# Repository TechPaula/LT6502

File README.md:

# GITHUB PROJECT NOW DEAD
I've now moved away from Micros**t and it's AI slop.

Find this project here - (https://codeberg.org/TechPaula/)

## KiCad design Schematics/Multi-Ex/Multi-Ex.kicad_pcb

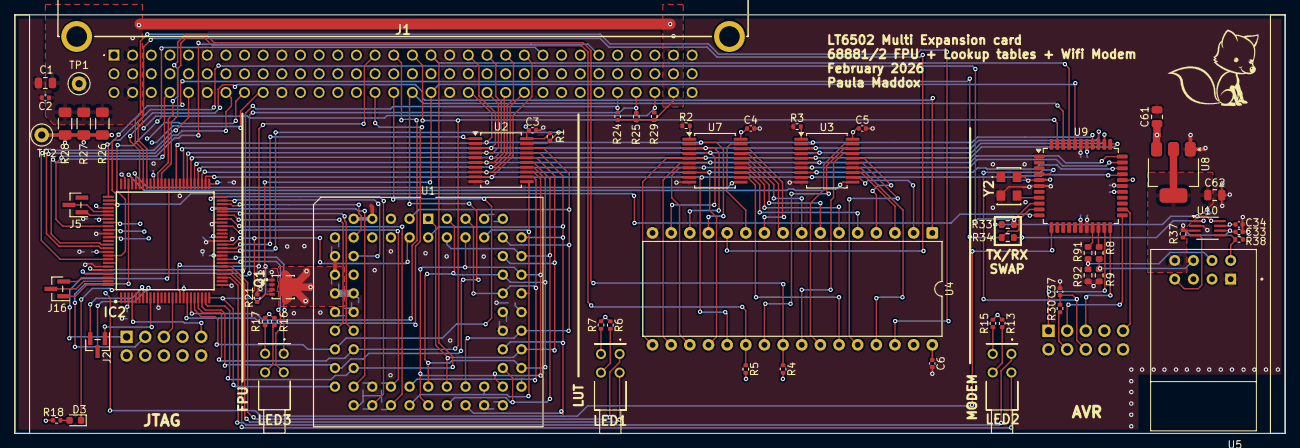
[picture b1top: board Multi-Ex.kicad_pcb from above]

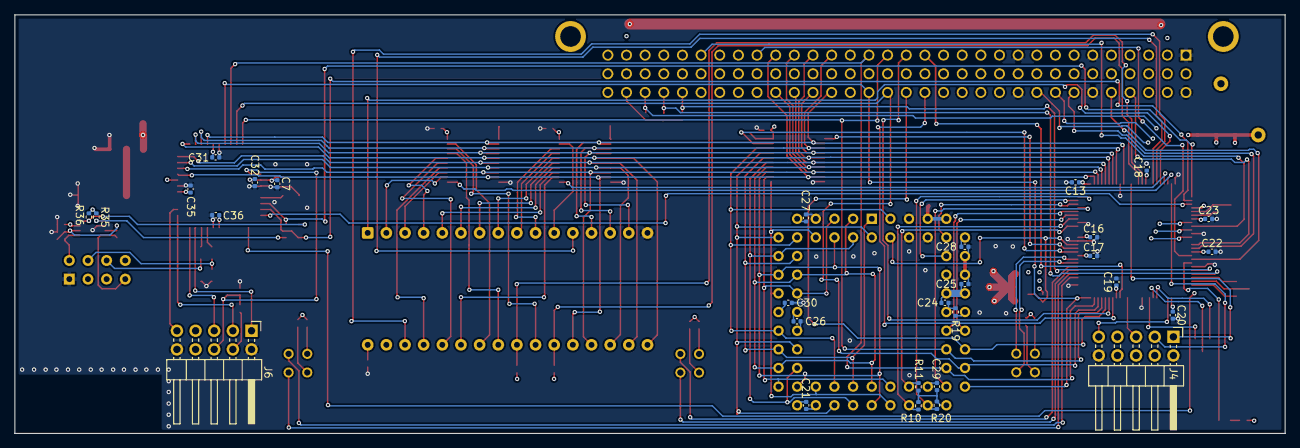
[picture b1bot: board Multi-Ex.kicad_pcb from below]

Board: 4 copper layers, 173.0 x 57.0 mm, 91 parts (29 on the bottom side), 120 nets.

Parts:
C1: 22uF 25V; C_0805_2012Metric
C2, C3, C4, C5, C6, C7, C13, C16, C17, C18, C19, C20, C21, C22, C23, C24, C25, C26, C27, C28, C29, C30, C31, C32, C33, C34, C35, C36, C37: 100nF; C_0402_1005Metric
C61, C62: 10uF NP; C_0805_2012Metric
D3: LED; LED_0603_1608Metric
FOX1: SYM_Flash_Large; Fox_avatar_18mm
IC2: ATF1508AS-7AX100; QFP50P1600X1600X120-100N
J1: DIN41612_02x32_AC(CAPS); 86093967113745ELF
J2, J5, J16: Conn_01x03; PinHeader_1x03_P1.00mm_Vertical_SMD_Pin1Left
J4, J6: Conn_02x05_Odd_Even; PinHeader_2x05_P2.54mm_Horizontal
LED1, LED2, LED3: LTL-42D1NMHDP1; LTL42D1NMHDP1
Q1: STL9P3LLH6; STL20N6F7
R1, R4, R5, R10, R11, R20, R24, R25, R29, R30, R35, R36, R37, R38: 10K; R_0402_1005Metric
R2, R3, R19: 0R; R_0402_1005Metric
R6, R7, R13, R15, R16, R17, R18: 470R; R_0402_1005Metric
R8, R91: 1K8; R_0603_1608Metric
R9, R92: 3K3; R_0603_1608Metric
R21: 100K; R_0402_1005Metric
R26, R27, R28: 0R; R_1206_3216Metric_Pad1.30x1.75mm_HandSolder
R33, R34: 0R; R_0603_1608Metric
TP1, TP2: TestPoint; TestPoint_Loop_D1.80mm_Drill1.0mm_Beaded
U1: MC68882_PLCC_68; PLCC-68_THT-Socket
U2: 74HC245; SSOP-20_5.3x7.2mm_P0.65mm
U3, U7: 74LS573; SSOP-20_5.3x7.2mm_P0.65mm
U4: SST39SF040; DIP-32_W15.24mm
U5: ESP8266-01_ESP-01; XCVR_ESP8266-01_ESP-01
U8: AMS1117-3.3; SOT-223-3_TabPin2
U9: ATmega644P-20A; TQFP-44_10x10mm_P0.8mm
U10: TXS0102DCT; SSOP-8_2.95x2.8mm_P0.65mm
Y2: ECS-3961-200-AU-TR; ECS3961200AUTR

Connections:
+3.3V: C33.1, C62.1, R37.1, R38.1, U5.8 (VCC), U8.2 (VO), U10.3 (VCCA), U10.6 (OE)
+5V: C3.1, C4.1, C5.1, C6.1, C7.1, C13.1, C16.1, C17.1, C18.1, C19.1, C20.1, C22.1, C23.1, C31.1, C32.1, C34.1, C35.1, C36.1, C61.1, IC2.3 (VCCIO_1), IC2.18 (VCCIO_2), IC2.34 (VCCIO_3), IC2.39 (VCCINT_1), IC2.51 (VCCIO_4), IC2.66 (VCCIO_5), IC2.82 (VCCIO_6), IC2.91 (VCCINT_2), J4.4, J6.4, Q1.1 (S_1), Q1.2 (S_2), Q1.3 (S_3), R1.2, R4.2, R5.2, R6.1, R7.2, R13.1, R15.2, R16.1, R17.2, R18.2, R21.1, R26.2, R27.2, R28.2, R30.1, R35.1, R36.1, TP2.1, U2.20 (VCC), U3.20 (VCC), U4.32 (VCC), U7.20 (VCC), U8.3 (VI), U9.5 (VCC), U9.17 (VCC), U9.27 (AVCC), U9.29 (AREF), U9.38 (VCC), U10.7 (VCCB), Y2.4 (VDD)
/Connector/A0: IC2.25 (I/O_19), J1.C18, U1.26 (A0), U9.40 (PB0)
/Connector/A1: IC2.24 (I/O_18), J1.A18, U1.25 (A1), U9.41 (PB1)
/Connector/A2: IC2.23 (I/O_17), J1.C17, U1.24 (A2), U9.42 (PB2)
/Connector/A3: IC2.22 (I/O_16), J1.A17, U1.23 (A3), U9.43 (PB3)
/Connector/A4: IC2.21 (I/O_15), J1.C16, U1.22 (A4)
/Connector/A5: IC2.20 (I/O_14), J1.A16
/Connector/A6: IC2.19 (I/O_13), J1.C15
/Connector/A7: IC2.17 (I/O_12), J1.A15
/Connector/CLK: IC2.87 (INPUT/GCLK1), J1.C9
/Connector/CLK/2: IC2.85 (I/O/GCLK3), J1.C8
/Connector/CPU_CLK: IC2.90 (INPUT/OE2/GCLK2), J1.C7
/Connector/D0: IC2.60 (I/O_46), J1.C20, U2.2 (A0), U3.2 (D0), U4.13 (D0), U7.2 (D0), U9.37 (PA0)
/Connector/D1: IC2.58 (I/O_45), J1.A20, U2.3 (A1), U3.3 (D1), U4.14 (D1), U7.3 (D1), U9.36 (PA1)
/Connector/D2: IC2.57 (I/O_44), J1.C21, U2.4 (A2), U3.4 (D2), U4.15 (D2), U7.4 (D2), U9.35 (PA2)
/Connector/D3: IC2.56 (I/O_43), J1.A21, U2.5 (A3), U3.5 (D3), U4.17 (D3), U7.5 (D3), U9.34 (PA3)
/Connector/D4: IC2.55 (I/O_42), J1.C22, U2.6 (A4), U3.6 (D4), U4.18 (D4), U7.6 (D4), U9.33 (PA4)
/Connector/D5: IC2.54 (I/O_41), J1.A22, U2.7 (A5), U3.7 (D5), U4.19 (D5), U7.7 (D5), U9.32 (PA5)
/Connector/D6: IC2.53 (I/O_40), J1.C23, U2.8 (A6), U3.8 (D6), U4.20 (D6), U7.8 (D6), U9.31 (PA6)
/Connector/D7: IC2.52 (I/O_39), J1.A23, U2.9 (A7), U3.9 (D7), U4.21 (D7), U7.9 (D7), U9.30 (PA7)
/Connector/EXP_nSEL: IC2.83 (I/O_64), J1.C30, R29.2
/Connector/RDY: IC2.92 (I/O_66), J1.A24
/Connector/RnW: IC2.89 (INPUT/GCLR), J1.C4
/Connector/nIRQ: IC2.84 (I/O_65), J1.A27
/Connector/nRES: IC2.93 (I/O_67), J1.C5
/Connector/nSLOW0: IC2.96 (I/O_69), J1.C28, R24.2
/Connector/nSLOW1: IC2.97 (I/O_70), J1.C29, R25.2
/FPU/Dint0: U1.3 (D0), U1.40 (D24), U1.50 (D16), U1.62 (D8), U2.18 (B0)
/FPU/Dint1: U1.2 (D1), U1.39 (D25), U1.49 (D17), U1.60 (D9), U2.17 (B1)
/FPU/Dint2: U1.1 (D2), U1.38 (D26), U1.48 (D18), U1.59 (D10), U2.16 (B2)
/FPU/Dint3: U1.37 (D27), U1.47 (D19), U1.58 (D11), U1.68 (D3), U2.15 (B3)
/FPU/Dint4: U1.36 (D28), U1.46 (D20), U1.57 (D12), U1.67 (D4), U2.14 (B4)
/FPU/Dint5: U1.35 (D29), U1.45 (D21), U1.56 (D13), U1.66 (D5), U2.13 (B5)
/FPU/Dint6: U1.34 (D30), U1.44 (D22), U1.55 (D14), U1.65 (D6), U2.12 (B6)
/FPU/Dint7: U1.33 (D31), U1.42 (D23), U1.54 (D15), U1.64 (D7), U2.11 (B7)
/FPU/FPU_BUF_DIR: IC2.36 (I/O_28), U2.1 (A->B)
/FPU/FPU_CLK: IC2.48 (I/O_36), U1.11 (CLK)
/FPU/FPU_RnW: IC2.47 (I/O_35), U1.28 (R/*W)
/FPU/FPU_nAS: IC2.46 (I/O_34), U1.21 (*AS)
/FPU/FPU_nBUFEN: IC2.35 (I/O_27), R1.1, U2.19 (CE)
/FPU/FPU_nCS: IC2.50 (I/O_38), R20.2, U1.29 (*CS)
/FPU/FPU_nDS: IC2.45 (I/O_33), U1.20 (*DS)
/FPU/FPU_nDSACK0: IC2.44 (I/O_32), R10.2, U1.31 (*DSACK0)
/FPU/FPU_nDSACK1: IC2.42 (I/O_31), R11.2, U1.32 (*DSACK1)
/FPU/FPU_nRESET: IC2.49 (I/O_37), U1.13 (*RESET)
/GLUE/LUT_BYTE0: IC2.71 (I/O_55), U7.11 (Load)
/GLUE/LUT_BYTE1: IC2.72 (I/O_56), U3.11 (Load)
/GLUE/LUT_FUNC0: IC2.69 (I/O_53), U4.30 (A17)
/GLUE/LUT_FUNC1: IC2.70 (I/O_54), U4.1 (A18)
/GLUE/LUT_RES_HnL: IC2.68 (I/O_52), U4.12 (A0)
/GLUE/LUT_nCS: IC2.64 (I/O_49), R5.1, U4.22 (CE)
/GLUE/LUT_nOE: IC2.65 (I/O_50), R4.1, U4.24 (OE)
/GLUE/MODEM_RX_LED: IC2.29 (I/O_22), LED2.3 (K_2)
/GLUE/MODEM_RnW: IC2.79 (I/O_61), U9.12 (PD3)
/GLUE/MODEM_TX_LED: IC2.28 (I/O_21), LED2.1 (K_1)
/GLUE/MODEM_nCS: IC2.78 (I/O_60), U9.11 (PD2)
/LookUpTable/LUT0: U4.11 (A1), U7.19 (Q0)
/LookUpTable/LUT1: U4.10 (A2), U7.18 (Q1)
/LookUpTable/LUT2: U4.9 (A3), U7.17 (Q2)
/LookUpTable/LUT3: U4.8 (A4), U7.16 (Q3)
/LookUpTable/LUT4: U4.7 (A5), U7.15 (Q4)
/LookUpTable/LUT5: U4.6 (A6), U7.14 (Q5)
/LookUpTable/LUT6: U4.5 (A7), U7.13 (Q6)
/LookUpTable/LUT7: U4.27 (A8), U7.12 (Q7)
/LookUpTable/LUT8: U3.19 (Q0), U4.26 (A9)
/LookUpTable/LUT9: U3.18 (Q1), U4.23 (A10)
/LookUpTable/LUT10: U3.17 (Q2), U4.25 (A11)
/LookUpTable/LUT11: U3.16 (Q3), U4.4 (A12)
/LookUpTable/LUT12: U3.15 (Q4), U4.28 (A13)
/LookUpTable/LUT13: U3.14 (Q5), U4.29 (A14)
/LookUpTable/LUT14: U3.13 (Q6), U4.3 (A15)
/LookUpTable/LUT15: U3.12 (Q7), U4.2 (A16)
/Modem/ESP01_EN: R91.1, U9.19 (PC0)
/Modem/ESP01_nRST: R8.1, U9.20 (PC1)
/Modem/RX_3V3: R37.2, U5.4 (RXD), U10.4 (A2)
/Modem/RX_5V: IC2.76 (I/O_58), R33.2, U9.9 (PD0)
/Modem/TX_3V3: R38.2, U5.5 (TXD), U10.5 (A1)
/Modem/TX_5V: IC2.77 (I/O_59), R34.2, U9.10 (PD1)
AVR_TCK: J6.1, U9.21 (PC2)
AVR_TDI: J6.9, U9.24 (PC5)
AVR_TDO: J6.3, U9.23 (PC4)
AVR_TMS: J6.5, U9.22 (PC3)
AVR_nRST: C37.1, J6.6, R30.2, U9.4 (~RESET)
CONN_5V: C1.1, C2.1, J1.A2, J1.A31, J1.C2, J1.C31, R24.1, R25.1, R26.1, R27.1, R28.1, R29.1, TP1.1
FPU_5V: C21.1, C24.1, C25.1, C26.1, C27.1, C28.1, C29.1, C30.1, Q1.5 (D), Q1.6 (D), Q1.7 (D), R10.1, R11.1, R20.1, U1.10 (VCC), U1.16 (VCC), U1.17 (VCC), U1.27 (VCC), U1.43 (VCC), U1.52 (VCC), U1.53 (VCC), U1.61 (VCC)
FPU_LED0: IC2.33 (I/O_26), LED3.1 (K_1)
FPU_LED1: IC2.32 (I/O_25), LED3.3 (K_2)
FPU_nSENSE: IC2.37 (I/O_29), Q1.4 (G), R21.2, U1.4 (*SENSE)
GND: C1.2, C2.2, C3.2, C4.2, C5.2, C6.2, C7.2, C13.2, C16.2, C17.2, C18.2, C19.2, C20.2, C21.2, C22.2, C23.2, C24.2, C25.2, C26.2, C27.2, C28.2, C29.2, C30.2, C31.2, C32.2, C33.2, C34.2, C35.2, C36.2, C37.2, C61.2, C62.2, IC2.11 (GND_1), IC2.26 (GND_2), IC2.38 (GND_3), IC2.43 (GND_4), IC2.59 (GND_5), IC2.74 (GND_6), IC2.86 (GND_7), IC2.95 (GND_8), J1.A1, J1.A6, J1.A10, J1.A19, J1.A32, J1.C1, J1.C6, J1.C10, J1.C19, J1.C32, J4.2, J4.10, J6.2, J6.10, R2.1, R3.1, R9.2, R19.1, R92.2, U1.5 (GND), U1.6 (GND), U1.7 (GND), U1.8 (GND), U1.9 (GND), U1.12 (GND), U1.14 (GND), U1.19 (GND), U1.30 (GND), U1.41 (GND), U1.51 (GND), U1.63 (GND), U2.10 (GND), U3.10 (GND), U4.16 (GND), U5.1 (GND), U7.10 (GND), U8.1 (GND), U9.6 (GND), U9.18 (GND), U9.28 (GND), U9.39 (GND), U10.2 (GND), Y2.2 (GROUND)
LUT_LED0: IC2.31 (I/O_24), LED1.1 (K_1)
LUT_LED1: IC2.30 (I/O_23), LED1.3 (K_2)
unnamed: D3.2 (A), R18.1
unnamed: D3.1 (K), IC2.94 (I/O_68)
unnamed: IC2.7 (I/O_4), J2.3
unnamed: IC2.8 (I/O_5), J2.2
unnamed: IC2.9 (I/O_6), J2.1
unnamed: IC2.80 (I/O_62), J5.2
unnamed: IC2.81 (I/O_63), J5.1
unnamed: IC2.98 (I/O_71), J16.3
unnamed: IC2.99 (I/O_72), J16.2
unnamed: IC2.100 (I/O_73), J16.1
unnamed: LED1.2 (A_1), R7.1
unnamed: LED1.4 (A_2), R6.2
unnamed: LED2.2 (A_1), R15.1
unnamed: LED2.4 (A_2), R13.2
unnamed: LED3.2 (A_1), R17.1
unnamed: LED3.4 (A_2), R16.2
unnamed: R19.2, U1.18 (SIZE)
unnamed: R3.2, U3.1 (OE)
unnamed: R91.2, R92.1, U5.6 (EN)
unnamed: R8.2, R9.1, U5.7 (~RST)
unnamed: R2.2, U7.1 (OE)
unnamed: U9.8 (XTAL1), Y2.3 (OUTPUT)
unnamed: R33.1, R36.2, U10.8 (B1)
unnamed: R34.1, R35.2, U10.1 (B2)
TCK: IC2.62 (I/O/TCK), J4.1
TDI: IC2.4 (I/O/TDI), J4.9
TDO: IC2.73 (I/O/TDO), J4.3
TMS: IC2.15 (I/O/TMS), J4.5

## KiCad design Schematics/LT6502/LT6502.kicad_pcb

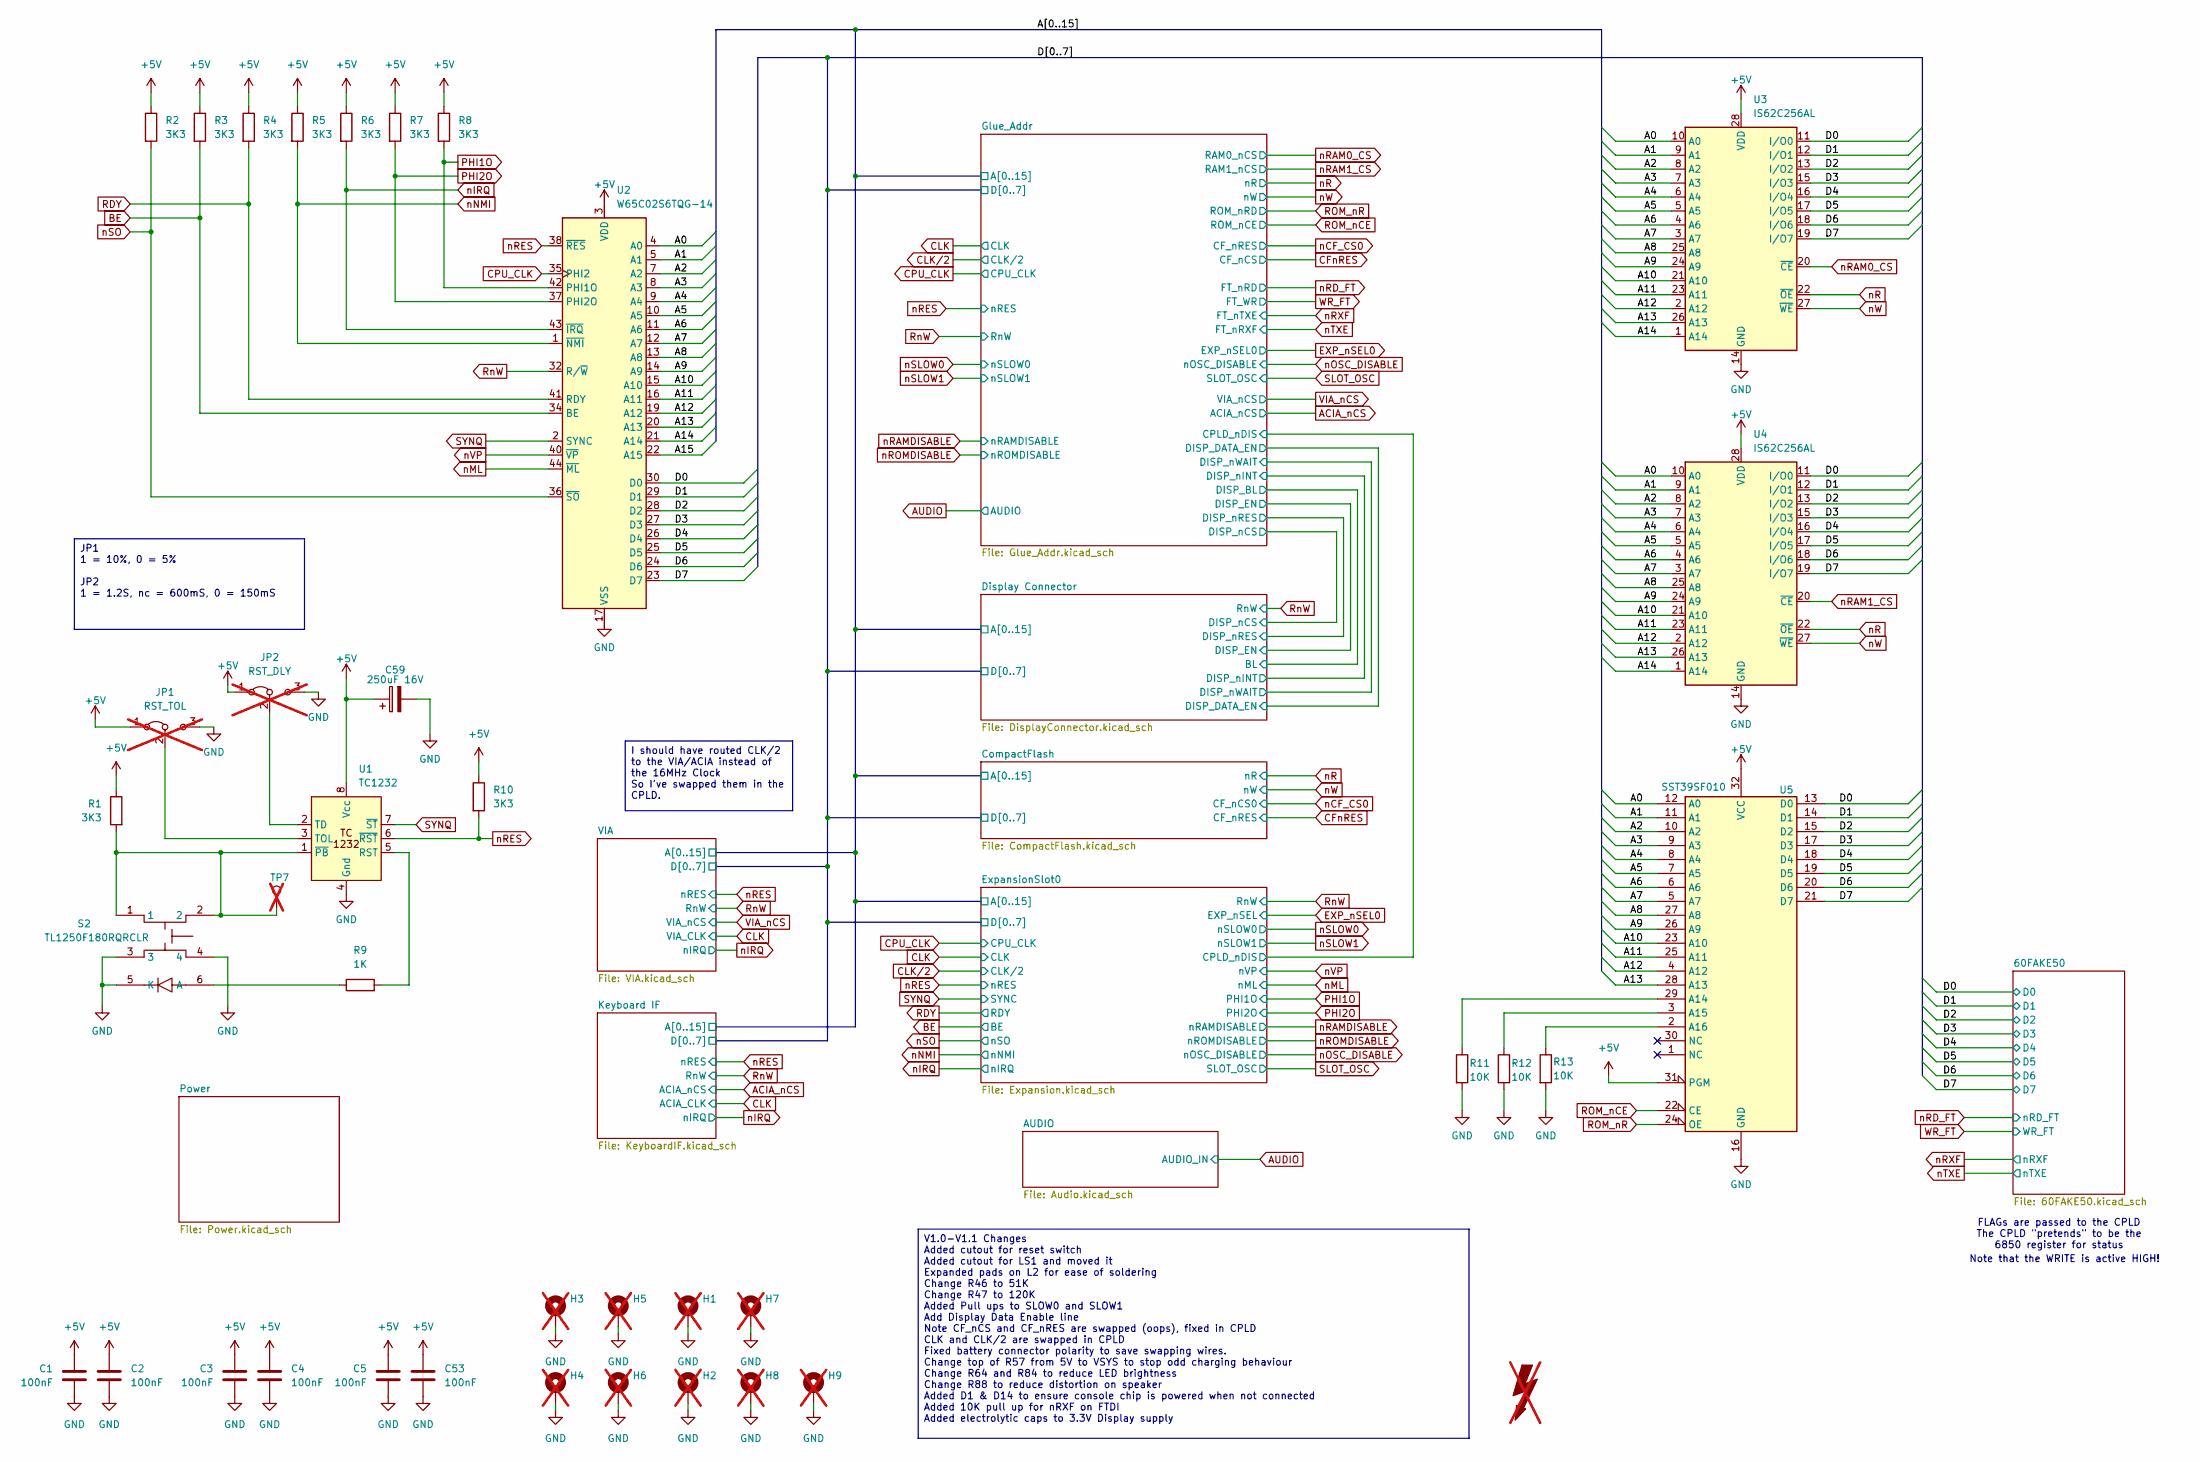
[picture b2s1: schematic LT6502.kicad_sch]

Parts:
C1, C2, C3, C4, C5, C53: 100nF; C_0603_1608Metric; LCSC C113803
C59: 250uF 16V; CP_Elec_10x12.5; Mouser Part Number 667-EEV-FK1V681Q
FOX1: SYM_Flash_Large; Fox_avatar_18mm; LCSC DNF; not fitted
H1, H2, H3, H4, H5, H6, H7, H8, H9: MountingHole_Pad; MountingHole_3.2mm_M3_Pad_TopBottom; LCSC DNF; not fitted
JP1: RST_TOL; SolderJumper-3_P1.3mm_Bridged12_Pad1.0x1.5mm_NumberLabels; LCSC DNF; not fitted
JP2: RST_DLY; SolderJumper-3_P1.3mm_Bridged12_Pad1.0x1.5mm_NumberLabels; LCSC DNF; not fitted
R1, R2, R3, R4, R5, R6, R7, R8, R10: 3K3; R_0402_1005Metric; LCSC C25890
R9: 1K; R_0402_1005Metric; LCSC C11702
R11, R12, R13: 10K; R_0402_1005Metric; LCSC C25744
S2: TL1250F180RQRCLR; Mouser Part Number 612-TL1250F180RQRCLR
TP7: TestPoint; TestPoint_Loop_D1.80mm_Drill1.0mm_Beaded; LCSC DNF; not fitted
U1: TC1232; DIP-8_W7.62mm_LongPads; Mouser Part Number 579-TC1232CPA
U2: W65C02S6TQG-14; QFP80P1320X1320X270-44N; Mouser Part Number 955-W65C02S6TQG-14
U3, U4: IS62C256AL; SOP-28_8.4x18.16mm_P1.27mm; Mouser Part Number 870-62C256AL-25ULIT
U5: SST39SF010; DIP-32_W15.24mm_Socket; LCSC DNF

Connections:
+5V: C1.1, C2.1, C3.1, C4.1, C5.1, C53.1, C59.1, JP1.1 (A), JP2.1 (A), R1.1, R2.1, R3.1, R4.1, R5.1, R6.1, R7.1, R8.1, R10.1, U1.8 (Vcc), U2.3 (VDD), U2.31 (VDD), U3.28 (VDD), U4.28 (VDD), U5.31 (PGM), U5.32 (VCC); also elsewhere on the board
/A0: U2.4 (A0), U3.10 (A0), U4.10 (A0), U5.12 (A0); also elsewhere on the board
/A1: U2.5 (A1), U3.9 (A1), U4.9 (A1), U5.11 (A1); also elsewhere on the board
/A2: U2.7 (A2), U3.8 (A2), U4.8 (A2), U5.10 (A2); also elsewhere on the board
/A3: U2.8 (A3), U3.7 (A3), U4.7 (A3), U5.9 (A3); also elsewhere on the board
/A4: U2.9 (A4), U3.6 (A4), U4.6 (A4), U5.8 (A4); also elsewhere on the board
/A5: U2.10 (A5), U3.5 (A5), U4.5 (A5), U5.7 (A5); also elsewhere on the board
/A6: U2.11 (A6), U3.4 (A6), U4.4 (A6), U5.6 (A6); also elsewhere on the board
/A7: U2.12 (A7), U3.3 (A7), U4.3 (A7), U5.5 (A7); also elsewhere on the board
/A8: U2.13 (A8), U3.25 (A8), U4.25 (A8), U5.27 (A8); also elsewhere on the board
/A9: U2.14 (A9), U3.24 (A9), U4.24 (A9), U5.26 (A9); also elsewhere on the board
/A10: U2.15 (A10), U3.21 (A10), U4.21 (A10), U5.23 (A10); also elsewhere on the board
/A11: U2.16 (A11), U3.23 (A11), U4.23 (A11), U5.25 (A11); also elsewhere on the board
/A12: U2.19 (A12), U3.2 (A12), U4.2 (A12), U5.4 (A12); also elsewhere on the board
/A13: U2.20 (A13), U3.26 (A13), U4.26 (A13), U5.28 (A13); also elsewhere on the board
/A14: U2.21 (A14), U3.1 (A14), U4.1 (A14); also elsewhere on the board
/A15: U2.22 (A15); also elsewhere on the board
/D0: U2.30 (D0), U3.11 (I/O0), U4.11 (I/O0), U5.13 (D0); also elsewhere on the board
/D1: U2.29 (D1), U3.12 (I/O1), U4.12 (I/O1), U5.14 (D1); also elsewhere on the board
/D2: U2.28 (D2), U3.13 (I/O2), U4.13 (I/O2), U5.15 (D2); also elsewhere on the board
/D3: U2.27 (D3), U3.15 (I/O3), U4.15 (I/O3), U5.17 (D3); also elsewhere on the board
/D4: U2.26 (D4), U3.16 (I/O4), U4.16 (I/O4), U5.18 (D4); also elsewhere on the board
/D5: U2.25 (D5), U3.17 (I/O5), U4.17 (I/O5), U5.19 (D5); also elsewhere on the board
/D6: U2.24 (D6), U3.18 (I/O6), U4.18 (I/O6), U5.20 (D6); also elsewhere on the board
/D7: U2.23 (D7), U3.19 (I/O7), U4.19 (I/O7), U5.21 (D7); also elsewhere on the board
BE: R3.2, U2.34 (BE); also elsewhere on the board
CPU_CLK: U2.35 (PHI2); also elsewhere on the board
GND: C1.2, C2.2, C3.2, C4.2, C5.2, C53.2, C59.2, H1.1, H2.1, H3.1, H4.1, H5.1, H6.1, H7.1, H8.1, H9.1, JP1.3 (B), JP2.3 (B), R11.2, R12.2, R13.2, S2.3, S2.4, S2.5 (K), U1.4 (Gnd), U2.17 (VSS), U2.18 (VSS), U2.39 (VSS), U3.14 (GND), U4.14 (GND), U5.16 (GND); also elsewhere on the board
unnamed: JP1.2 (C), U1.3 (TOL)
unnamed: JP2.2 (C), U1.2 (TD)
unnamed: R9.1, S2.6 (A)
unnamed: R9.2, U1.5 (RST)
unnamed: R1.2, S2.1, S2.2, TP7.1, U1.1 (~PB)
unnamed: R11.1, U5.29 (A14)
unnamed: R12.1, U5.3 (A15)
unnamed: R13.1, U5.2 (A16)
PHI1O: R8.2, U2.42 (PHI1O); also elsewhere on the board
PHI2O: R7.2, U2.37 (PHI2O); also elsewhere on the board
RDY: R4.2, U2.41 (RDY); also elsewhere on the board
ROM_nCE: U5.22 (CE); also elsewhere on the board
ROM_nR: U5.24 (OE); also elsewhere on the board
RnW: U2.32 (R/~W); also elsewhere on the board
SYNQ: U1.7 (~ST), U2.2 (SYNC); also elsewhere on the board
nIRQ: R6.2, U2.43 (~IRQ); also elsewhere on the board
nML: U2.44 (~ML); also elsewhere on the board
nNMI: R5.2, U2.1 (~NMI); also elsewhere on the board
nR: U3.22 (~OE), U4.22 (~OE); also elsewhere on the board
nRAM0_CS: U3.20 (~CE); also elsewhere on the board
nRAM1_CS: U4.20 (~CE); also elsewhere on the board
nRES: R10.2, U1.6 (~RST), U2.38 (~RES); also elsewhere on the board
nSO: R2.2, U2.36 (~SO); also elsewhere on the board
nVP: U2.40 (~VP); also elsewhere on the board
nW: U3.27 (~WE), U4.27 (~WE); also elsewhere on the board

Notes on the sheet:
FLAGs are passed to the CPLD The CPLD "pretends" to be the 6850 register for status
Note that the WRITE is active HIGH!
JP1 1 = 10%, 0 = 5% JP2 1 = 1.2S, nc = 600mS, 0 = 150mS
I should have routed CLK/2 to the VIA/ACIA instead of the 16MHz Clock So I've swapped them in the CPLD.
V1.0-V1.1 Changes Added cutout for reset switch Added cutout for LS1 and moved it Expanded pads on L2 for ease of soldering Change R46 to 51K Change R47 to 120K Added Pull ups to SLOW0 and SLOW1 Add Display Data Enable line Note CF_nCS and CF_nRES are swapped (oops), fixed in CPLD CLK and CLK/2 are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

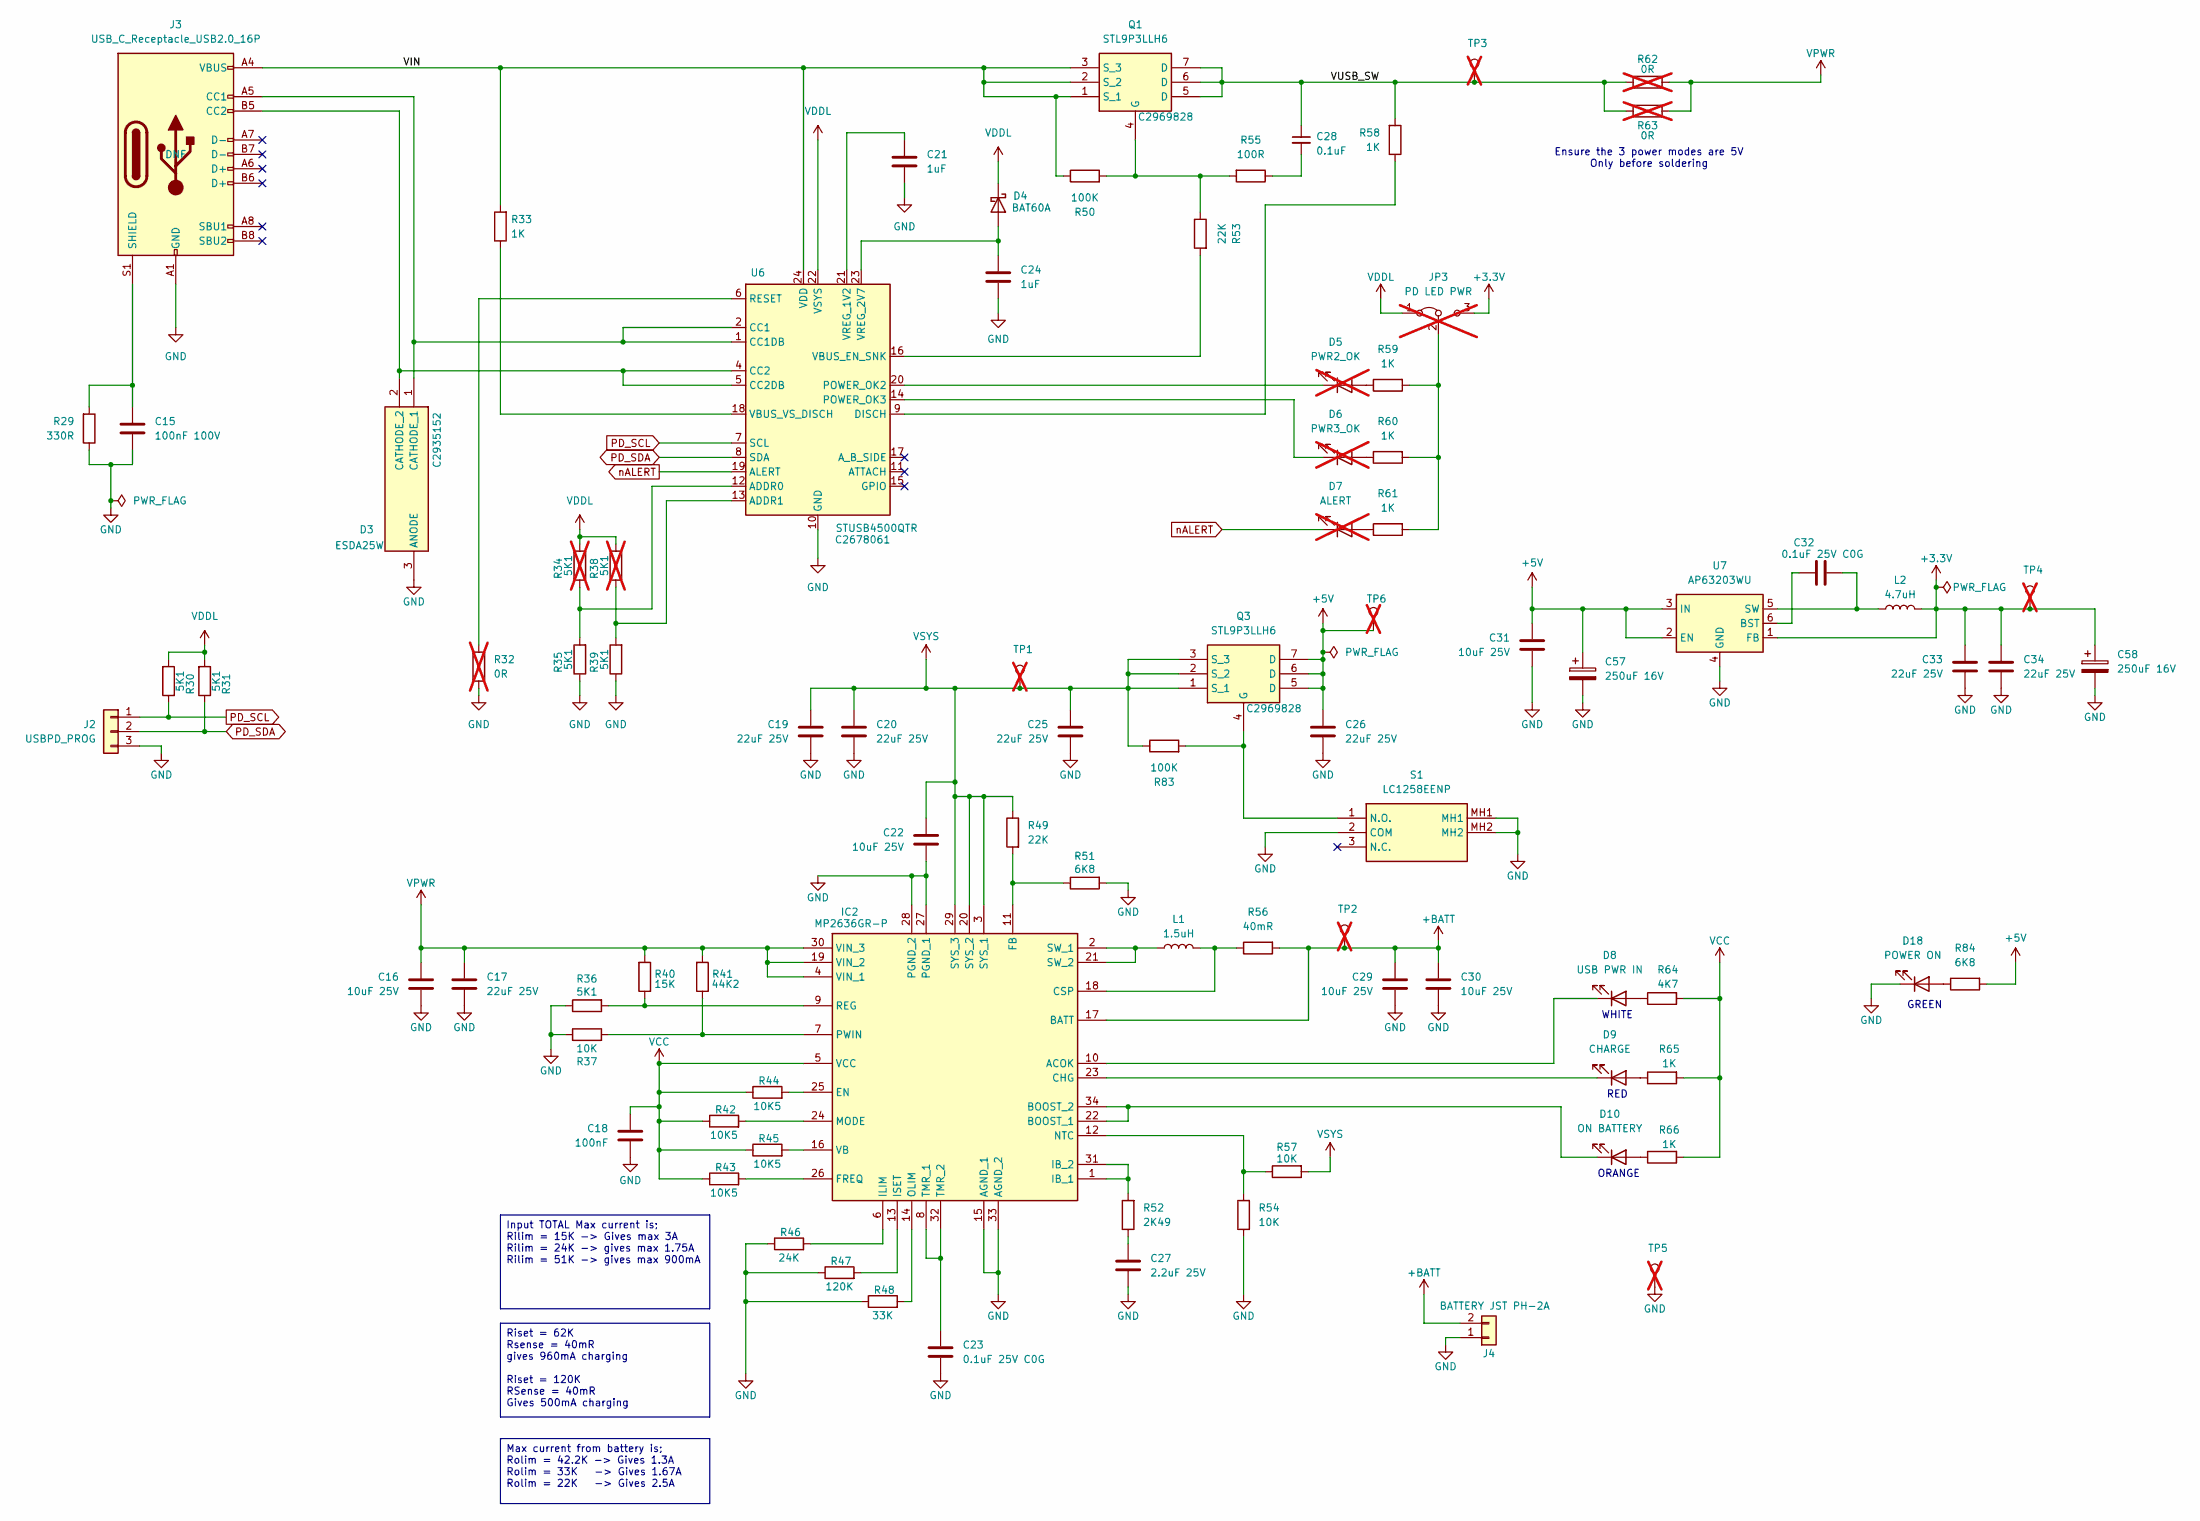
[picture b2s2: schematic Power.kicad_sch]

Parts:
C15: 100nF 100V; C_0603_1608Metric; LCSC C113803
C16, C22, C29, C30, C31: 10uF 25V; C_0805_2012Metric; LCSC C15850
C17, C19, C20, C25, C26, C33, C34: 22uF 25V; C_0805_2012Metric; LCSC C45783
C18: 100nF; C_0603_1608Metric; LCSC C113803
C21, C24: 1uF; C_0603_1608Metric; LCSC C15849
C23, C32: 0.1uF 25V C0G; C_0603_1608Metric; LCSC C91183
C27: 2.2uF 25V; C_0805_2012Metric; LCSC C19110
C28: 0.1uF; C_0603_1608Metric; LCSC C113803
C57, C58: 250uF 16V; CP_Elec_10x12.5; Mouser Part Number 667-EEV-FK1V681Q
D3: ESDA25W; SOT65P210X110-3N; Mouser Part Number 511-ESDA25W
D4: BAT60A; D_SOD-323; LCSC C5355496
D5: PWR2_OK; LED_0603_1608Metric; LCSC DNF; not fitted
D6: PWR3_OK; LED_0603_1608Metric; LCSC DNF; not fitted
D7: ALERT; LED_0603_1608Metric; LCSC DNF; not fitted
D8: USB PWR IN; LED_0805_2012Metric; LCSC DNF
D9: CHARGE; LED_0805_2012Metric; LCSC DNF
D10: ON BATTERY; LED_0805_2012Metric; LCSC DNF
D18: POWER ON; LED_0805_2012Metric; LCSC DNF
IC2: MP2636GR-P; MP2636GR; Mouser Part Number 946-MP2636GR-P
J2: USBPD_PROG; PinHeader_1x03_P2.54mm_Vertical; LCSC DNF
J3: USB_C_Receptacle_USB2.0_16P; USB_C_Receptacle_HCTL_HC-TYPE-C-16P-01A; LCSC DNF
J4: BATTERY JST PH-2A; SHDRRA2W80P0X250_1X2_740X1150X610P; Mouser Part Number 306-S2B-XH-ALFSN
JP3: PD LED PWR; SolderJumper-3_P1.3mm_Bridged12_Pad1.0x1.5mm_NumberLabels; LCSC DNF; not fitted
L1: 1.5uH; INDPM6060X470N; Mouser Part Number 652-SRN6045HA-1R5Y
L2: 4.7uH; NRS5020T220MMGJV; Mouser Part Number 963-NRS5020T4R7MMGJ
Q1, Q3: STL9P3LLH6; STL20N6F7; Manufacturer_Part_Number STL9P3LLH6; Mouser Part Number 511-STL9P3LLH6
R29: 330R; R_0402_1005Metric; LCSC C25104
R30, R31, R35, R36, R39: 5K1; R_0402_1005Metric; LCSC C25905
R32: 0R; R_0402_1005Metric; LCSC DNF; not fitted
R33, R58, R59, R60, R61, R65, R66: 1K; R_0402_1005Metric; LCSC C11702
R34, R38: 5K1; R_0402_1005Metric; LCSC C25905; not fitted
R37, R54, R57: 10K; R_0402_1005Metric; LCSC C25744
R40: 15K; R_0402_1005Metric; LCSC C25756
R41: 44K2; R_0402_1005Metric; LCSC C11565
R42, R43, R44, R45: 10K5; R_0402_1005Metric; LCSC C25850
R46: 24K; R_0402_1005Metric; LCSC ???
R47: 120K; R_0402_1005Metric; LCSC ???
R48: 33K; R_0402_1005Metric
R49, R53: 22K; R_0402_1005Metric; LCSC C25768
R50, R83: 100K; R_0402_1005Metric; LCSC C25741
R51: 6K8; R_0402_1005Metric; LCSC C25917
R52: 2K49; R_0402_1005Metric; LCSC C2692737
R55: 100R; R_0402_1005Metric; LCSC C25076
R56: 40mR; R_1206_3216Metric; LCSC C2774938
R62, R63: 0R; R_0603_1608Metric; LCSC DNF; not fitted
R64: 4K7; R_0402_1005Metric
R84: 6K8; R_0402_1005Metric
S1: LC1258EENP; Mouser Part Number 612-LC1258EENP
TP1, TP2, TP3, TP4, TP5, TP6: TestPoint; TestPoint_Loop_D1.80mm_Drill1.0mm_Beaded; LCSC DNF; not fitted
U6: STUSB4500QTR; QFN-24-1EP_4x4mm_P0.5mm_EP2.7x2.7mm; LCSC C2678061
U7: AP63203WU; TSOT-23-6; Mouser Part Number 621-AP63203WU-7

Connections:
+3.3V: C33.1, C34.1, C58.1, JP3.3 (B), L2.2, TP4.1, U7.1 (FB); also elsewhere on the board
+5V: C26.1, C31.1, C57.1, Q3.5 (D), Q3.6 (D), Q3.7 (D), R84.2, TP6.1, U7.2 (EN), U7.3 (IN); also elsewhere on the board
+BATT: C29.1, C30.1, IC2.17 (BATT), J4.2, R56.2, TP2.1
/Power/VIN: J3.A4 (VBUS), J3.A9 (VBUS), J3.B4 (VBUS), J3.B9 (VBUS), Q1.1 (S_1), Q1.2 (S_2), Q1.3 (S_3), R33.2, R50.1, U6.24 (VDD)
/Power/VUSB_SW: C28.1, Q1.5 (D), Q1.6 (D), Q1.7 (D), R58.2, R62.1, R63.1, TP3.1
GND: C15.2, C16.2, C17.2, C18.2, C19.2, C20.2, C21.2, C22.2, C23.2, C24.2, C25.2, C26.2, C27.2, C29.2, C30.2, C31.2, C33.2, C34.2, C57.2, C58.2, D3.3 (ANODE), D18.1 (K), IC2.15 (AGND_1), IC2.27 (PGND_1), IC2.28 (PGND_2), IC2.33 (AGND_2), J2.3, J3.A1 (GND), J3.A12 (GND), J3.B1 (GND), J3.B12 (GND), J4.1, R29.1, R32.1, R35.1, R36.1, R37.1, R39.1, R46.1, R47.1, R48.1, R51.2, R54.1, S1.2 (COM), S1.MH1, S1.MH2, TP5.1, U6.10 (GND), U6.25 (GND), U7.4 (GND); also elsewhere on the board
unnamed: C27.1, R52.1
unnamed: C28.2, R55.1
unnamed: D3.1 (CATHODE_1), J3.A5 (CC1), U6.1 (CC1DB), U6.2 (CC1)
unnamed: D3.2 (CATHODE_2), J3.B5 (CC2), U6.4 (CC2), U6.5 (CC2DB)
unnamed: C24.1, D4.2 (A), U6.23 (VREG_2V7)
unnamed: D5.2 (A), R59.1
unnamed: D5.1 (K), U6.20 (POWER_OK2)
unnamed: D6.2 (A), R60.1
unnamed: D6.1 (K), U6.14 (POWER_OK3)
unnamed: D7.2 (A), R61.1
unnamed: D8.2 (A), R64.1
unnamed: D8.1 (K), IC2.10 (ACOK)
unnamed: D9.2 (A), R65.1
unnamed: D9.1 (K), IC2.23 (CHG)
unnamed: D10.2 (A), R66.1
unnamed: D10.1 (K), IC2.22 (BOOST_1), IC2.34 (BOOST_2)
unnamed: D18.2 (A), R84.1
unnamed: IC2.18 (CSP), L1.2, R56.1
unnamed: IC2.25 (EN), R44.2
unnamed: IC2.11 (FB), R49.2, R51.1
unnamed: IC2.26 (FREQ), R43.2
unnamed: IC2.1 (IB_1), IC2.31 (IB_2), R52.2
unnamed: IC2.6 (ILIM), R46.2
unnamed: IC2.13 (ISET), R47.2
unnamed: IC2.24 (MODE), R42.2
unnamed: IC2.12 (NTC), R54.2, R57.1
unnamed: IC2.14 (OLIM), R48.2
unnamed: IC2.7 (PWIN), R37.2, R41.1
unnamed: IC2.9 (REG), R36.2, R40.1
unnamed: IC2.2 (SW_1), IC2.21 (SW_2), L1.1
unnamed: C23.1, IC2.8 (TMR_1), IC2.32 (TMR_2)
unnamed: IC2.16 (VB), R45.2
unnamed: C15.1, J3.S1 (SHIELD), R29.2
unnamed: JP3.2 (C), R59.2, R60.2, R61.2
unnamed: Q1.4 (G), R50.2, R53.1, R55.2
unnamed: Q3.4 (G), R83.2, S1.1 (N.O.)
unnamed: R34.1, R35.2, U6.12 (ADDR0)
unnamed: R38.1, R39.2, U6.13 (ADDR1)
unnamed: R58.1, U6.9 (DISCH)
unnamed: R32.2, U6.6 (RESET)
unnamed: R53.2, U6.16 (VBUS_EN_SNK)
unnamed: R33.1, U6.18 (VBUS_VS_DISCH)
unnamed: C21.1, U6.21 (VREG_1V2)
unnamed: C32.1, U7.6 (BST)
unnamed: C32.2, L2.1, U7.5 (SW)
PD_SCL: J2.1, R30.1, U6.7 (SCL)
PD_SDA: J2.2, R31.1, U6.8 (SDA)
VCC: C18.1, IC2.5 (VCC), R42.1, R43.1, R44.1, R45.1, R64.2, R65.2, R66.2
VDDL: D4.1 (K), JP3.1 (A), R30.2, R31.2, R34.2, R38.2, U6.22 (VSYS)
VPWR: C16.1, C17.1, IC2.4 (VIN_1), IC2.19 (VIN_2), IC2.30 (VIN_3), R40.2, R41.2, R62.2, R63.2
VSYS: C19.1, C20.1, C22.1, C25.1, IC2.3 (SYS_1), IC2.20 (SYS_2), IC2.29 (SYS_3), Q3.1 (S_1), Q3.2 (S_2), Q3.3 (S_3), R49.1, R57.2, R83.1, TP1.1
nALERT: D7.1 (K), U6.19 (ALERT)

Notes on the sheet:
Ensure the 3 power modes are 5V Only before soldering
ORANGE
RED
GREEN
WHITE
Input TOTAL Max current is; Rilim = 15K -> Gives max 3A Rilim = 24K -> gives max 1.75A Rilim = 51K -> gives max 900mA
Riset = 62K Rsense = 40mR gives 960mA charging Riset = 120K RSense = 40mR Gives 500mA charging
Max current from battery is; Rolim = 42.2K -> Gives 1.3A Rolim = 33K -> Gives 1.67A Rolim = 22K -> Gives 2.5A

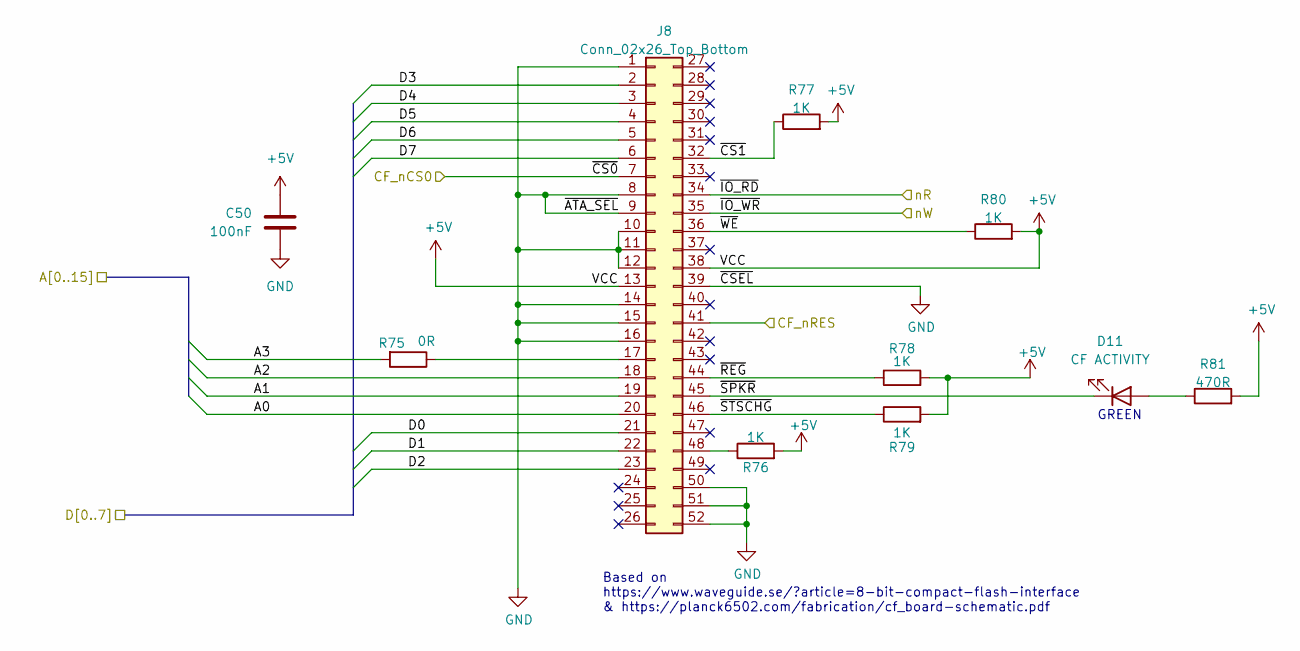
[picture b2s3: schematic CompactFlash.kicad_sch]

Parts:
C50: 100nF; C_0603_1608Metric; LCSC C113803
D11: CF ACTIVITY; LED_0805_2012Metric; LCSC DNF
J8: Conn_02x26_Top_Bottom; SD-SMD_CFH-L3C1LBL01MN0; Mouser Part Number 710-693120035011; LCSC DNF
R75: 0R; R_0402_1005Metric; LCSC DNF
R76, R77, R78, R79, R80: 1K; R_0402_1005Metric; LCSC C11702
R81: 470R; R_0402_1005Metric; LCSC C25117

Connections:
+5V: C50.1, J8.13, J8.38, R76.2, R77.2, R78.2, R79.2, R80.2, R81.2; also elsewhere on the board
/A0: J8.20; also elsewhere on the board
/A1: J8.19; also elsewhere on the board
/A2: J8.18; also elsewhere on the board
/A3: R75.2; also elsewhere on the board
/CompactFlash/~CS1: J8.32, R77.1
/CompactFlash/~REG: J8.44, R78.1
/CompactFlash/~SPKR: D11.1 (K), J8.45
/CompactFlash/~STSCHG: J8.46, R79.1
/CompactFlash/~WE: J8.36, R80.1
/D0: J8.21; also elsewhere on the board
/D1: J8.22; also elsewhere on the board
/D2: J8.23; also elsewhere on the board
/D3: J8.2; also elsewhere on the board
/D4: J8.3; also elsewhere on the board
/D5: J8.4; also elsewhere on the board
/D6: J8.5; also elsewhere on the board
/D7: J8.6; also elsewhere on the board
CFnRES: J8.41; also elsewhere on the board
GND: C50.2, J8.1, J8.8, J8.9, J8.10, J8.11, J8.12, J8.14, J8.15, J8.16, J8.39, J8.50, J8.51, J8.52; also elsewhere on the board
unnamed: D11.2 (A), R81.1
unnamed: J8.17, R75.1
unnamed: J8.48, R76.1
nCF_CS0: J8.7; also elsewhere on the board
nR: J8.34; also elsewhere on the board
nW: J8.35; also elsewhere on the board

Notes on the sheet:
GREEN
Based on https://www.waveguide.se/?article=8-bit-compact-flash-interface & https://planck6502.com/fabrication/cf_board-schematic.pdf
